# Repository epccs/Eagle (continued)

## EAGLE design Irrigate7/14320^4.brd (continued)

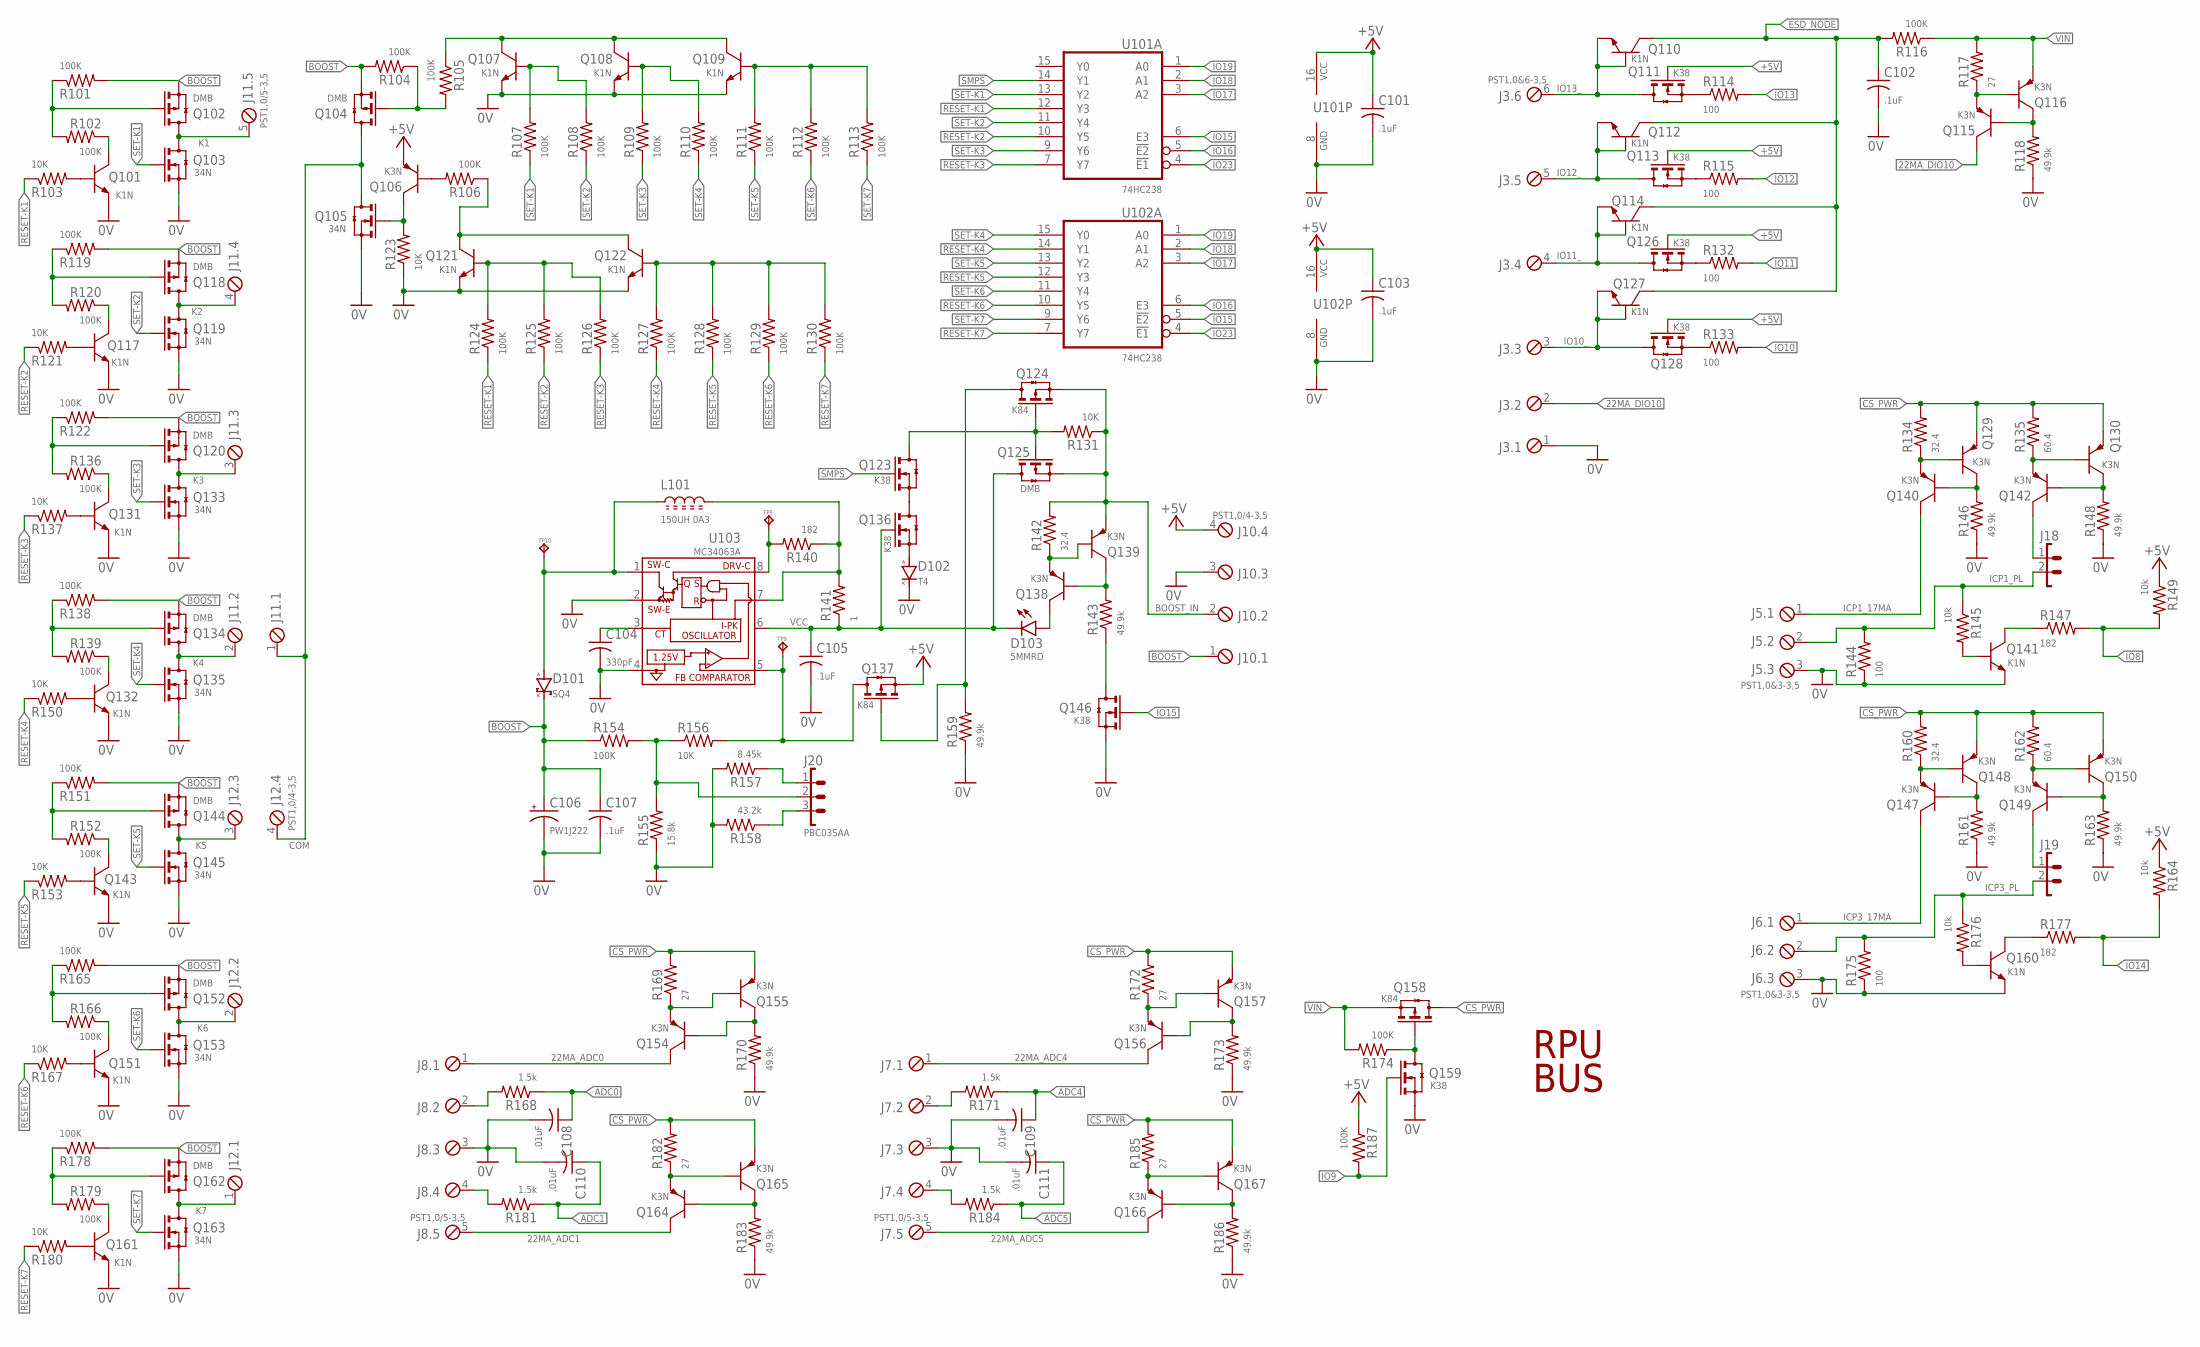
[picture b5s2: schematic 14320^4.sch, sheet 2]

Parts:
C101, C102, C103, C105, C107: .1uF; C0603(1608)
C104: 330pF; C0603(1608)
C106: PW1J222; E7,5-18
C108, C109, C110, C111: .01uF; C0603(1608)
D101: SQ4; SMA
D102: T4; SOD123
D103: 5MMRD; LED5MM
J3: PST1,0&6-3,5; MCV6
J5, J6: PST1,0&3-3,5; MCV3
J7, J8, J11: PST1,0/5-3,5; MCV5
J10, J12: PST1,0/4-3,5; MCV4
J18, J19: 1X2
J20: PBC03SAA; 1X3
L101: 150UH 0A3; L2626
Q101, Q107, Q108, Q109, Q110, Q112, Q114, Q117, Q121, Q122, Q127, Q131, Q132, Q141, Q143, Q151, Q160, Q161: K1N; SOT23
Q102, Q104, Q118, Q120, Q125, Q134, Q144, Q152, Q162: DMB; SOT23
Q103, Q105, Q119, Q133, Q135, Q145, Q153, Q163: 34N; SOT23
Q106, Q115, Q116, Q129, Q130, Q138, Q139, Q140, Q142, Q147, Q148, Q149, Q150, Q154, Q155, Q156, Q157, Q164, Q165, Q166, Q167: K3N; SOT23
Q111, Q113, Q123, Q126, Q128, Q136, Q146, Q159: K38; SOT23
Q124, Q137, Q158: K84; SOT23
R101, R102, R104, R105, R106, R107, R108, R109, R110, R111, R112, R113, R116, R119, R120, R122, R124, R125, R126, R127, R128, R129, R130, R136, R138, R139, R151, R152, R154, R165, R166, R174, R178, R179, R187: 100K; C0805(2012)
R103, R121, R123, R131, R137, R150, R153, R156, R167, R180: 10K; C0805(2012)
R114, R115, R132, R133, R144, R175: 100; C0805(2012)
R117, R169, R172, R182, R185: 27; C0805(2012)
R118, R143, R146, R148, R159, R161, R163, R170, R173, R183, R186: 49.9k; C0805(2012)
R134, R142, R160: 32.4; C0805(2012)
R135, R162: 60.4; C0805(2012)
R140, R147, R177: 182; C0805(2012)
R141: 1; C1210(3225)
R145, R149, R164, R176: 10k; C0805(2012)
R155: 15.8k; C0805(2012)
R157: 8.45k; C0805(2012)
R158: 43.2k; C0805(2012)
R168, R171, R181, R184: 1.5k; C0805(2012)
TP8, TP9, TP10: TPPAD1-08; P1-08
U101, U102: 74HC238; 16SOIC
U103: MC34063A; SOIC8

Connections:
0V: C101.2, C102.2, C103.2, C104.2, C105.2, C106.-, C107.2, C108.2, C109.2, C110.2, C111.2, D102.C (K), J3.1, J5.3, J6.3, J7.3, J8.3, J10.3, Q101.E, Q103.2(S) (S), Q105.2(S) (S), Q107.E, Q108.E, Q109.E, Q117.E, Q119.2(S) (S), Q121.E, Q122.E, Q131.E, Q132.E, Q133.2(S) (S), Q135.2(S) (S), Q141.E, Q143.E, Q145.2(S) (S), Q146.2(S) (S), Q151.E, Q153.2(S) (S), Q159.2(S) (S), Q160.E, Q161.E, Q163.2(S) (S), R118.1, R123.1, R144.1, R146.1, R148.1, R155.1, R157.2, R158.2, R159.1, R161.1, R163.1, R170.1, R173.1, R175.1, R183.1, R186.1, U101.8 (GND), U102.8 (GND), U103.2 (SW-E), U103.4 (GND); also elsewhere on the board
22MA_ADC0: J8.1, Q154.C
22MA_ADC1: J8.5, Q164.C
22MA_ADC4: J7.1, Q156.C
22MA_ADC5: J7.5, Q166.C
22MA_DIO10: J3.2, Q115.C
+5V: C101.1, C103.1, J10.4, Q106.E, Q111.1(G) (G), Q113.1(G) (G), Q126.1(G) (G), Q128.1(G) (G), Q137.2(S) (S), R149.1, R164.1, R187.1, U101.16 (VCC), U102.16 (VCC); also elsewhere on the board
ADC0: C108.1, R168.1; also elsewhere on the board
ADC1: C110.1, R181.1; also elsewhere on the board
ADC4: C109.1, R171.1; also elsewhere on the board
ADC5: C111.1, R184.1; also elsewhere on the board
BOOST: C106.+, C107.1, D101.K, J10.1, Q102.2(S) (S), Q104.2(S) (S), Q118.2(S) (S), Q120.2(S) (S), Q134.2(S) (S), Q144.2(S) (S), Q152.2(S) (S), Q162.2(S) (S), R101.2, R104.2, R119.2, R122.2, R138.2, R151.2, R154.1, R165.2, R178.2
BOOST17MA: Q146.3(D) (D), R143.1
BOOST_IN: J10.2, Q124.2(S) (S), Q125.2(S) (S), Q139.E, R131.1, R142.2
COM: J11.1, J12.4, Q104.3(D) (D), Q105.3(D) (D)
CS_PWR: Q129.E, Q130.E, Q148.E, Q150.E, Q155.E, Q157.E, Q158.3(D) (D), Q165.E, Q167.E, R134.2, R135.2, R160.2, R162.2, R169.2, R172.2, R182.2, R185.2
ESD_NODE: C102.1, Q110.C, Q112.C, Q114.C, Q127.C, R116.2; also elsewhere on the board
ICP1_17MA: J5.1, Q140.C
ICP1_PL: J5.2, J18.2, R144.2, R145.1
ICP3_17MA: J6.1, Q147.C
ICP3_PL: J6.2, J19.2, R175.2, R176.1
IO8: R147.2, R149.2; also elsewhere on the board
IO9: Q159.1(G) (G), R187.2; also elsewhere on the board
IO10: R133.2; also elsewhere on the board
IO10_: J3.3, Q127.B, Q127.E, Q128.3(D) (D)
IO11: R132.2; also elsewhere on the board
IO11_: J3.4, Q114.B, Q114.E, Q126.3(D) (D)
IO12: R115.2; also elsewhere on the board
IO12_: J3.5, Q112.B, Q112.E, Q113.3(D) (D)
IO13: R114.2; also elsewhere on the board
IO13_: J3.6, Q110.B, Q110.E, Q111.3(D) (D)
IO14: R164.2, R177.2; also elsewhere on the board
IO15: Q146.1(G) (G), U101.6 (E3), U102.5 (!E2); also elsewhere on the board
IO16: U101.5 (!E2), U102.6 (E3); also elsewhere on the board
IO17: U101.3 (A2), U102.3 (A2); also elsewhere on the board
IO18: U101.2 (A1), U102.2 (A1); also elsewhere on the board
IO19: U101.1 (A0), U102.1 (A0); also elsewhere on the board
IO23: U101.4 (!E1), U102.4 (!E1); also elsewhere on the board
K1: J11.5, Q102.3(D) (D), Q103.3(D) (D)
K2: J11.4, Q118.3(D) (D), Q119.3(D) (D)
K3: J11.3, Q120.3(D) (D), Q133.3(D) (D)
K4: J11.2, Q134.3(D) (D), Q135.3(D) (D)
K5: J12.3, Q144.3(D) (D), Q145.3(D) (D)
K6: J12.2, Q152.3(D) (D), Q153.3(D) (D)
K7: J12.1, Q162.3(D) (D), Q163.3(D) (D)
unnamed: Q123.2(S) (S), Q136.3(D) (D)
unnamed: Q124.3(D) (D), Q137.1(G) (G), R159.2
unnamed: D102.A, Q136.2(S) (S)
unnamed: Q137.3(D) (D), R156.2, TP9.TP, U103.5 (FB)
unnamed: Q104.1(G) (G), R104.1, R105.2
unnamed: Q154.E, Q155.B, R169.1
unnamed: Q129.B, Q140.E, R134.1
unnamed: R140.2, TP8.TP, U103.8 (DRV-C)
unnamed: L101.2, R140.1, R141.2, U103.7 (I-PK)
unnamed: D101.A, L101.1, TP10.TP, U103.1 (SW-C)
unnamed: C104.1, U103.3 (CT)
unnamed: Q129.C, Q140.B, R146.2
unnamed: Q130.B, Q142.E, R135.1
unnamed: J19.1, Q149.C
unnamed: Q130.C, Q142.B, R148.2
unnamed: Q105.1(G) (G), Q106.C, R123.2
unnamed: Q123.3(D) (D), Q124.1(G) (G), Q125.1(G) (G), R131.2
unnamed: Q154.B, Q155.C, R170.2
unnamed: J8.2, R168.2
unnamed: J20.2, R154.2, R155.2, R156.1
unnamed: Q107.C, Q108.C, Q109.C, R105.1
unnamed: Q109.B, R111.2, R112.2, R113.2
unnamed: Q108.B, R109.2, R110.2
unnamed: Q102.1(G) (G), R101.1, R102.2
unnamed: Q101.C, R102.1
unnamed: Q101.B, R103.2
unnamed: Q141.B, R145.2
unnamed: Q118.1(G) (G), R119.1, R120.2
unnamed: Q117.C, R120.1
unnamed: Q117.B, R121.2
unnamed: Q141.C, R147.1
unnamed: J8.4, R181.2
unnamed: Q120.1(G) (G), R122.1, R136.2
unnamed: Q131.C, R136.1
unnamed: Q131.B, R137.2
unnamed: Q134.1(G) (G), R138.1, R139.2
unnamed: Q132.C, R139.1
unnamed: Q132.B, R150.2
unnamed: Q144.1(G) (G), R151.1, R152.2
unnamed: Q143.C, R152.1
unnamed: Q143.B, R153.2
unnamed: Q107.B, R107.2, R108.2
unnamed: Q106.B, R106.2
unnamed: Q121.C, Q122.C, R106.1
unnamed: Q152.1(G) (G), R165.1, R166.2
unnamed: Q151.C, R166.1
unnamed: Q151.B, R167.2
unnamed: J18.1, Q142.C
unnamed: Q164.E, Q165.B, R182.1
unnamed: Q162.1(G) (G), R178.1, R179.2
unnamed: Q161.C, R179.1
unnamed: Q161.B, R180.2
unnamed: D103.A, Q138.C
unnamed: Q121.B, R124.2, R125.2, R126.2
unnamed: Q113.2(S) (S), R115.1
unnamed: Q164.B, Q165.C, R183.2
unnamed: Q156.E, Q157.B, R172.1
unnamed: Q156.B, Q157.C, R173.2
unnamed: J7.2, R171.2
unnamed: J7.4, R184.2
unnamed: Q166.E, Q167.B, R185.1
unnamed: Q166.B, Q167.C, R186.2
unnamed: Q158.1(G) (G), Q159.3(D) (D), R174.1
unnamed: Q111.2(S) (S), R114.1
unnamed: Q126.2(S) (S), R132.1
unnamed: Q160.B, R176.2
unnamed: Q160.C, R177.1
unnamed: Q128.2(S) (S), R133.1
unnamed: Q122.B, R127.2, R128.2, R129.2, R130.2
unnamed: Q147.E, Q148.B, R160.1
unnamed: Q147.B, Q148.C, R161.2
unnamed: J20.3, R158.1
unnamed: J20.1, R157.1
unnamed: Q149.E, Q150.B, R162.1
unnamed: Q149.B, Q150.C, R163.2
unnamed: Q115.E, Q116.B, R117.1
unnamed: Q115.B, Q116.C, R118.2
unnamed: Q138.E, Q139.B, R142.1
unnamed: Q138.B, Q139.C, R143.2
RESET-K1: R103.1, R124.1, U101.12 (Y3)
RESET-K2: R121.1, R125.1, U101.10 (Y5)
RESET-K3: R126.1, R137.1, U101.7 (Y7)
RESET-K4: R127.1, R150.1, U102.14 (Y1)
RESET-K5: R128.1, R153.1, U102.12 (Y3)
RESET-K6: R129.1, R167.1, U102.10 (Y5)
RESET-K7: R130.1, R180.1, U102.7 (Y7)
SET-K1: Q103.1(G) (G), R107.1, U101.13 (Y2)
SET-K2: Q119.1(G) (G), R108.1, U101.11 (Y4)
SET-K3: Q133.1(G) (G), R109.1, U101.9 (Y6)
SET-K4: Q135.1(G) (G), R110.1, U102.15 (Y0)
SET-K5: Q145.1(G) (G), R111.1, U102.13 (Y2)
SET-K6: Q153.1(G) (G), R112.1, U102.11 (Y4)
SET-K7: Q163.1(G) (G), R113.1, U102.9 (Y6)
SMPS: Q123.1(G) (G), U101.14 (Y1)
VCC: C105.1, D103.K, Q125.3(D) (D), Q136.1(G) (G), R141.1, U103.6 (VCC)
VIN: Q116.E, Q158.2(S) (S), R116.1, R117.2, R174.2; also elsewhere on the board

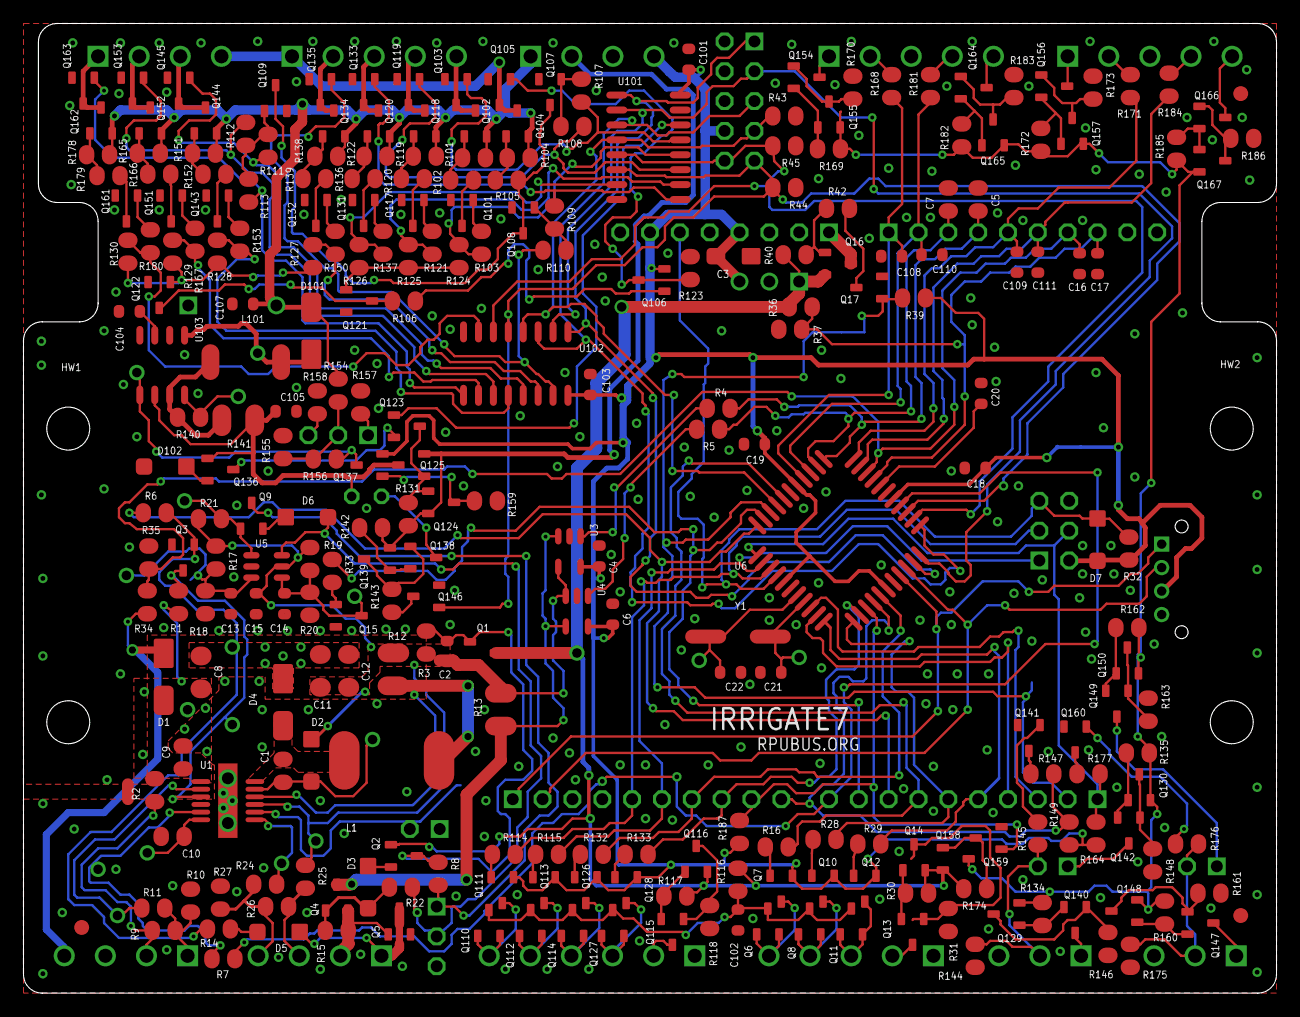
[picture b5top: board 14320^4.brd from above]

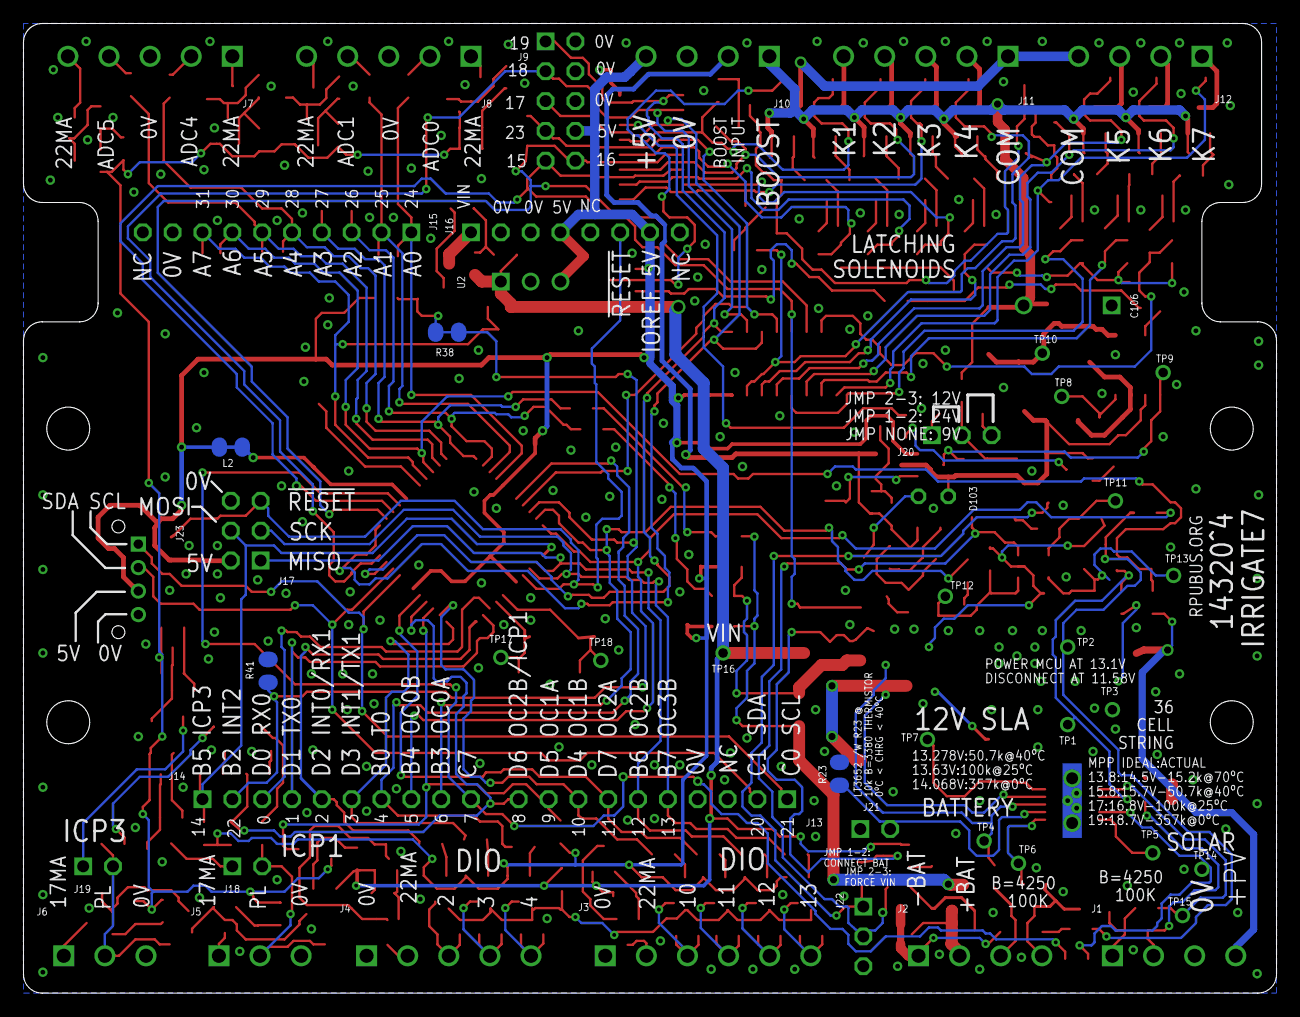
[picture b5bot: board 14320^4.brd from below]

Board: 2 copper layers, 106.7 x 82.5 mm, 319 parts (49 on the bottom side), 205 nets.

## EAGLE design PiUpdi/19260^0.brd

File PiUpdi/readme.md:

[PiUpdi]

Program a ATmega4809-PF with UPDI from R-Pi

[PiUpdi]: https://github.com/epccs/PiUpdi/

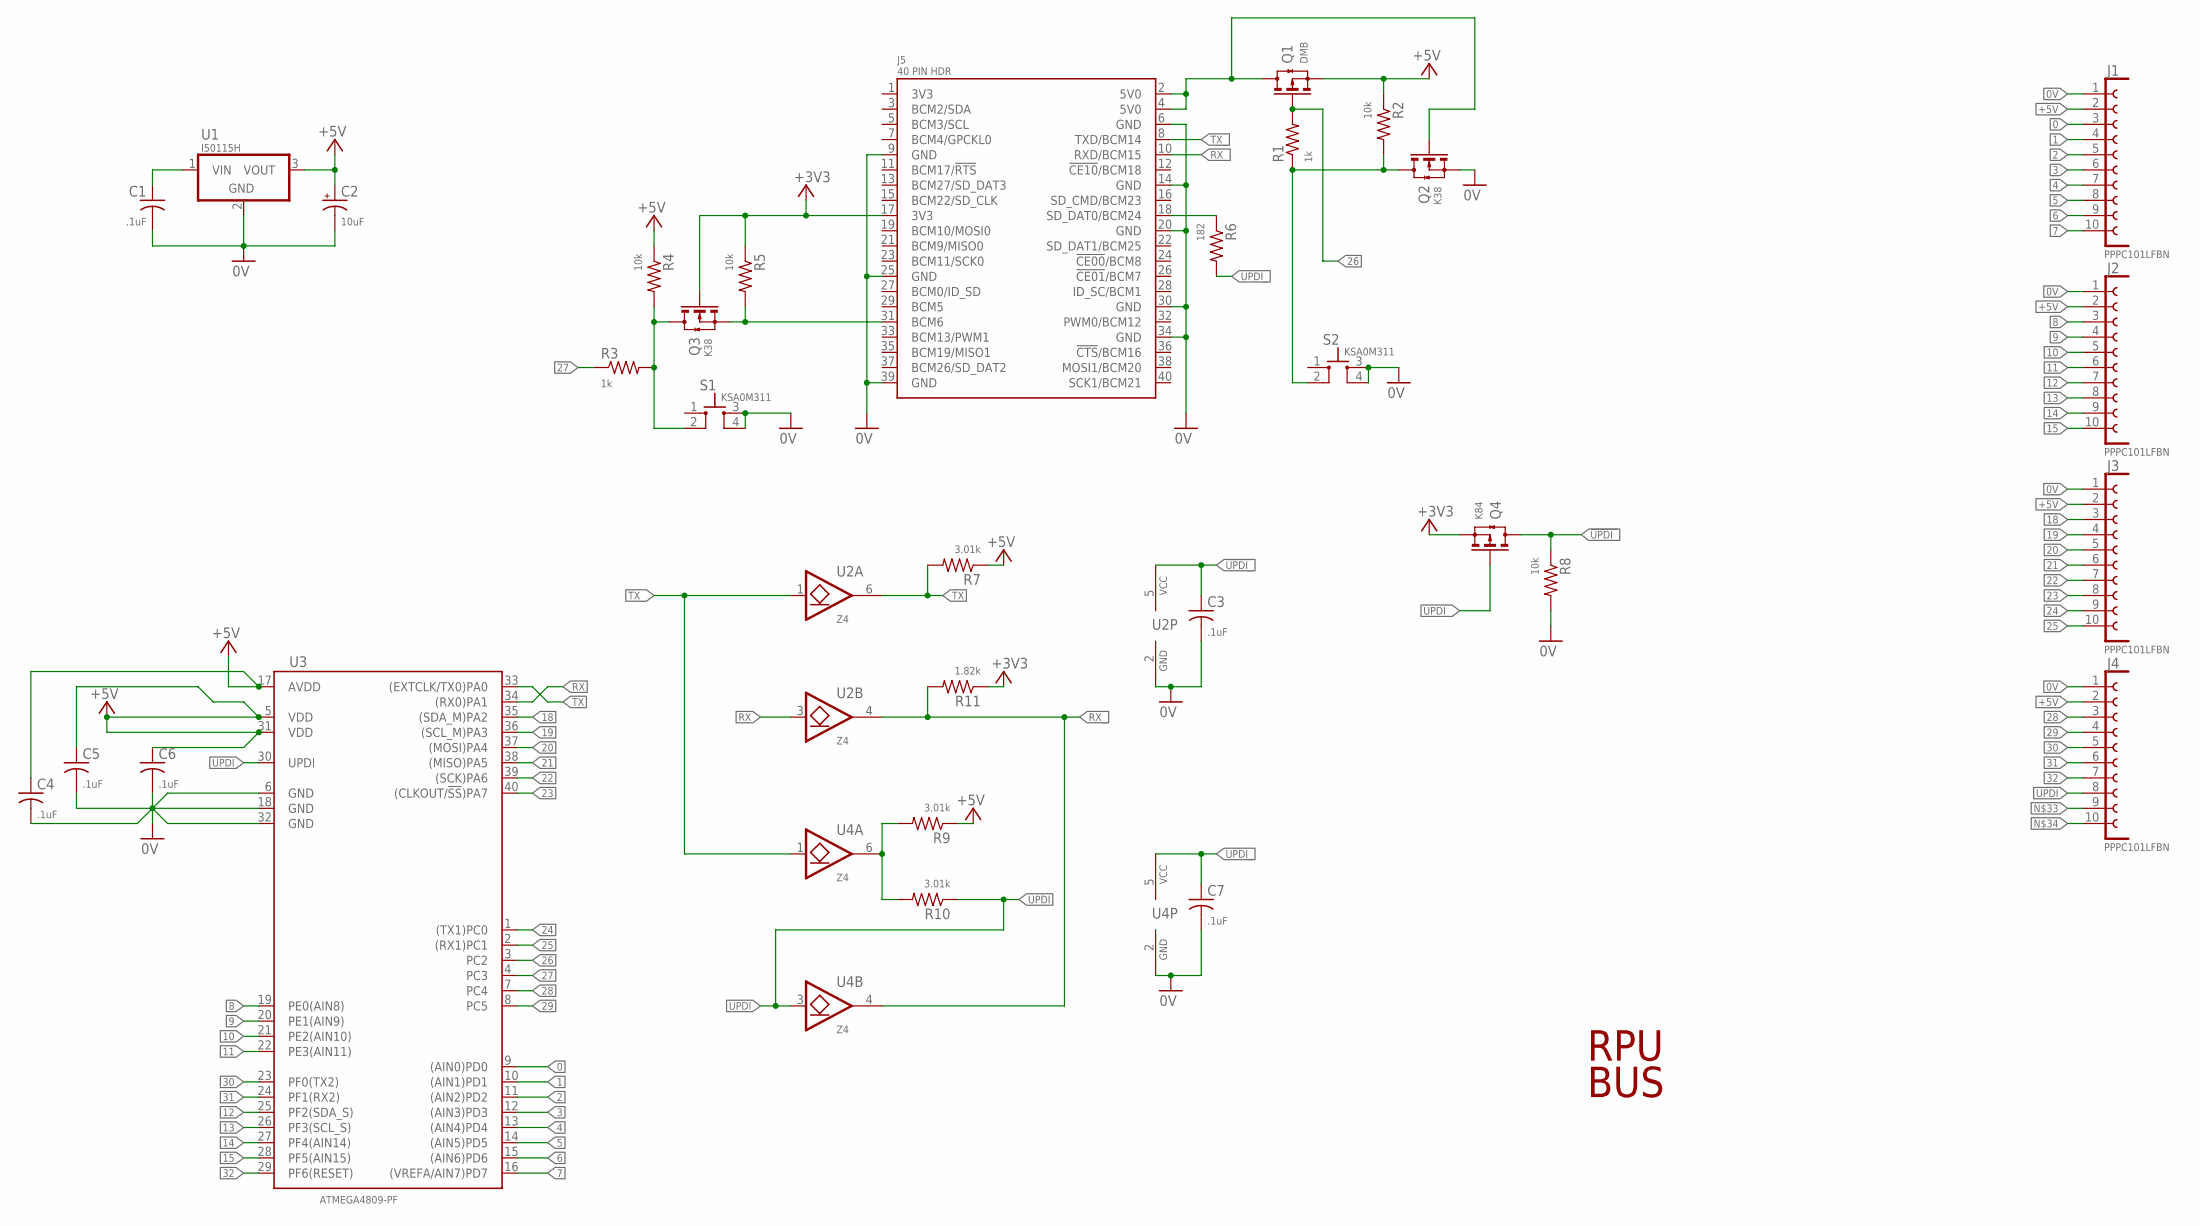
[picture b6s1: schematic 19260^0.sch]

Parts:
C1, C3, C4, C5, C6, C7: .1uF; C0603(1608)
C2: 10uF; 3216
J1, J2, J3, J4: PPPC101LFBN; F1X10
J5: 40 PIN HDR; RASPI_ZERO_H40PIN
Q1: DMB; SOT23
Q2, Q3: K38; SOT23
Q4: K84; SOT23
R1, R3: 1k; C0805(2012)
R2, R4, R5, R8: 10k; C0805(2012)
R6: 182; C0805(2012)
R7, R9, R10: 3.01k; C0805(2012)
R11: 1.82k; C0805(2012)
S1, S2: KSA0M311; 0M311
U1: I50115H; OKI-78SR-H
U2, U4: Z4; SOT23-6,SOT26
U3: ATMEGA4809-PF; DIL40

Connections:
0: J1.3, U3.9 ((AIN0)PD0)
0V: C1.2, C2.-, C3.2, C4.2, C5.2, C6.2, C7.2, J1.1, J2.1, J3.1, J4.1, J5.6 (GND), J5.9 (GND), J5.14 (GND), J5.20 (GND), J5.25 (GND), J5.30 (GND), J5.34 (GND), J5.39 (GND), Q2.2(S) (S), R8.2, S1.3, S1.4, S2.3, S2.4, U1.2 (GND), U2.2 (GND), U3.6 (GND), U3.18 (GND), U3.32 (GND), U4.2 (GND)
1: J1.4, U3.10 ((AIN1)PD1)
2: J1.5, U3.11 ((AIN2)PD2)
3: J1.6, U3.12 ((AIN3)PD3)
4: J1.7, U3.13 ((AIN4)PD4)
5: J1.8, U3.14 ((AIN5)PD5)
5V0@2: J5.2 (5V0), J5.4 (5V0), Q1.3(D) (D), Q2.1(G) (G)
6: J1.9, U3.15 ((AIN6)PD6)
7: J1.10, U3.16 ((VREFA/AIN7)PD7)
8: J2.3, U3.19 (PE0(AIN8))
9: J2.4, U3.20 (PE1(AIN9))
10: J2.5, U3.21 (PE2(AIN10))
11: J2.6, U3.22 (PE3(AIN11))
12: J2.7, U3.25 (PF2(SDA_S))
13: J2.8, U3.26 (PF3(SCL_S))
14: J2.9, U3.27 (PF4(AIN14))
15: J2.10, U3.28 (PF5(AIN15))
18: J3.3, U3.35 ((SDA_M)PA2)
19: J3.4, U3.36 ((SCL_M)PA3)
20: J3.5, U3.37 ((MOSI)PA4)
21: J3.6, U3.38 ((MISO)PA5)
22: J3.7, U3.39 ((SCK)PA6)
23: J3.8, U3.40 ((CLKOUT/!SS!)PA7)
24: J3.9, U3.1 ((TX1)PC0)
25: J3.10, U3.2 ((RX1)PC1)
26: Q1.1(G) (G), R1.2, U3.3 (PC2)
27: R3.1, U3.4 (PC3)
28: J4.3, U3.7 (PC4)
29: J4.4, U3.8 (PC5)
30: J4.5, U3.23 (PF0(TX2))
31: J4.6, U3.24 (PF1(RX2))
32: J4.7, U3.29 (PF6(RESET))
!UPDI_: C3.1, Q4.3(D) (D), R8.1, U2.5 (VCC)
+3V3: J5.17 (3V3), Q3.1(G) (G), Q4.2(S) (S), R5.1, R11.1
+5V: C2.+, C4.1, C5.1, C6.1, J1.2, J2.2, J3.2, J4.2, Q1.2(S) (S), R2.1, R4.1, R7.1, R9.1, U1.3 (VOUT), U3.5 (VDD), U3.17 (AVDD), U3.31 (VDD)
unnamed: J5.18 (SD_DAT0/BCM24), R6.1
unnamed: Q3.3(D) (D), R3.2, R4.2, S1.2
unnamed: R9.2, R10.2, U4.6 (O)
unnamed: Q2.3(D) (D), R1.1, R2.2, S2.2
RX: U2.3 (I), U3.34 ((RX0)PA1)
RX_: J5.10 (RXD/BCM15), R11.2, U2.4 (O), U4.4 (O)
SHUTDOWN: J5.31 (BCM6), Q3.2(S) (S), R5.2
TX: R7.2, U2.6 (O), U3.33 ((EXTCLK/TX0)PA0)
TX_: J5.8 (TXD/BCM14), U2.1 (I), U4.1 (I)
UPDI: J4.8, R10.1, U3.30 (UPDI), U4.3 (I)
UPDI_: C7.1, Q4.1(G) (G), R6.2, U4.5 (VCC)
VIN: C1.1, U1.1 (VIN)

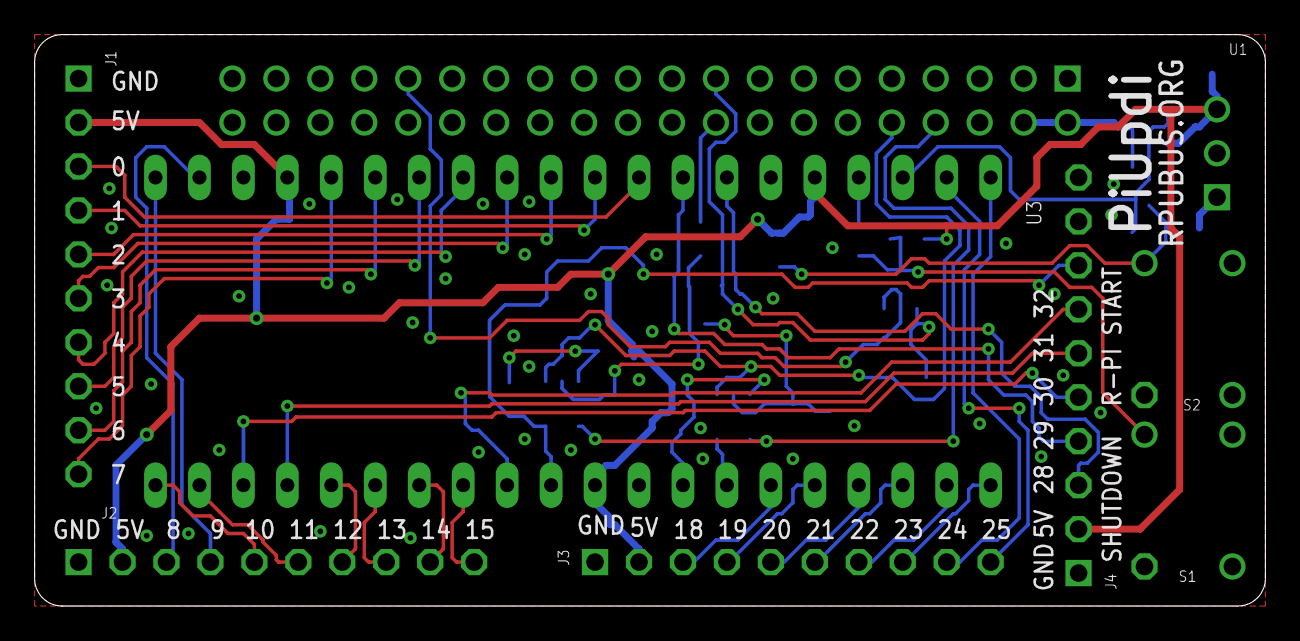
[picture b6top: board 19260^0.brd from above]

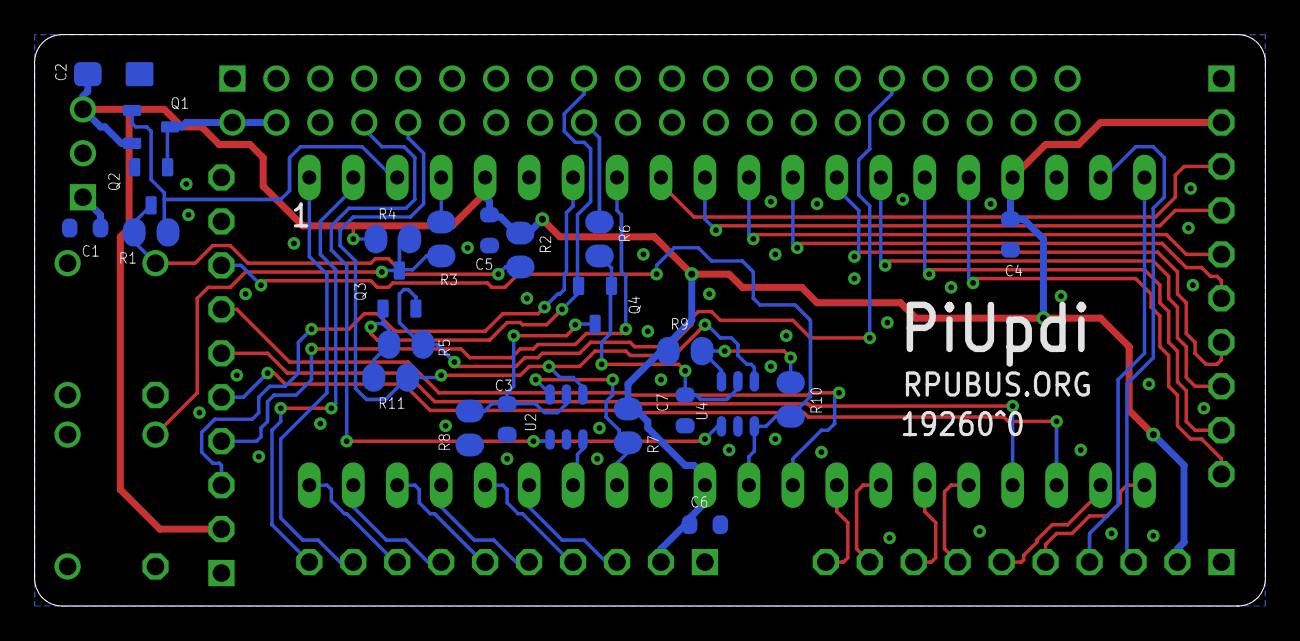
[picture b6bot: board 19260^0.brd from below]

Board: 2 copper layers, 71.1 x 33.0 mm, 33 parts (24 on the bottom side), 48 nets.
